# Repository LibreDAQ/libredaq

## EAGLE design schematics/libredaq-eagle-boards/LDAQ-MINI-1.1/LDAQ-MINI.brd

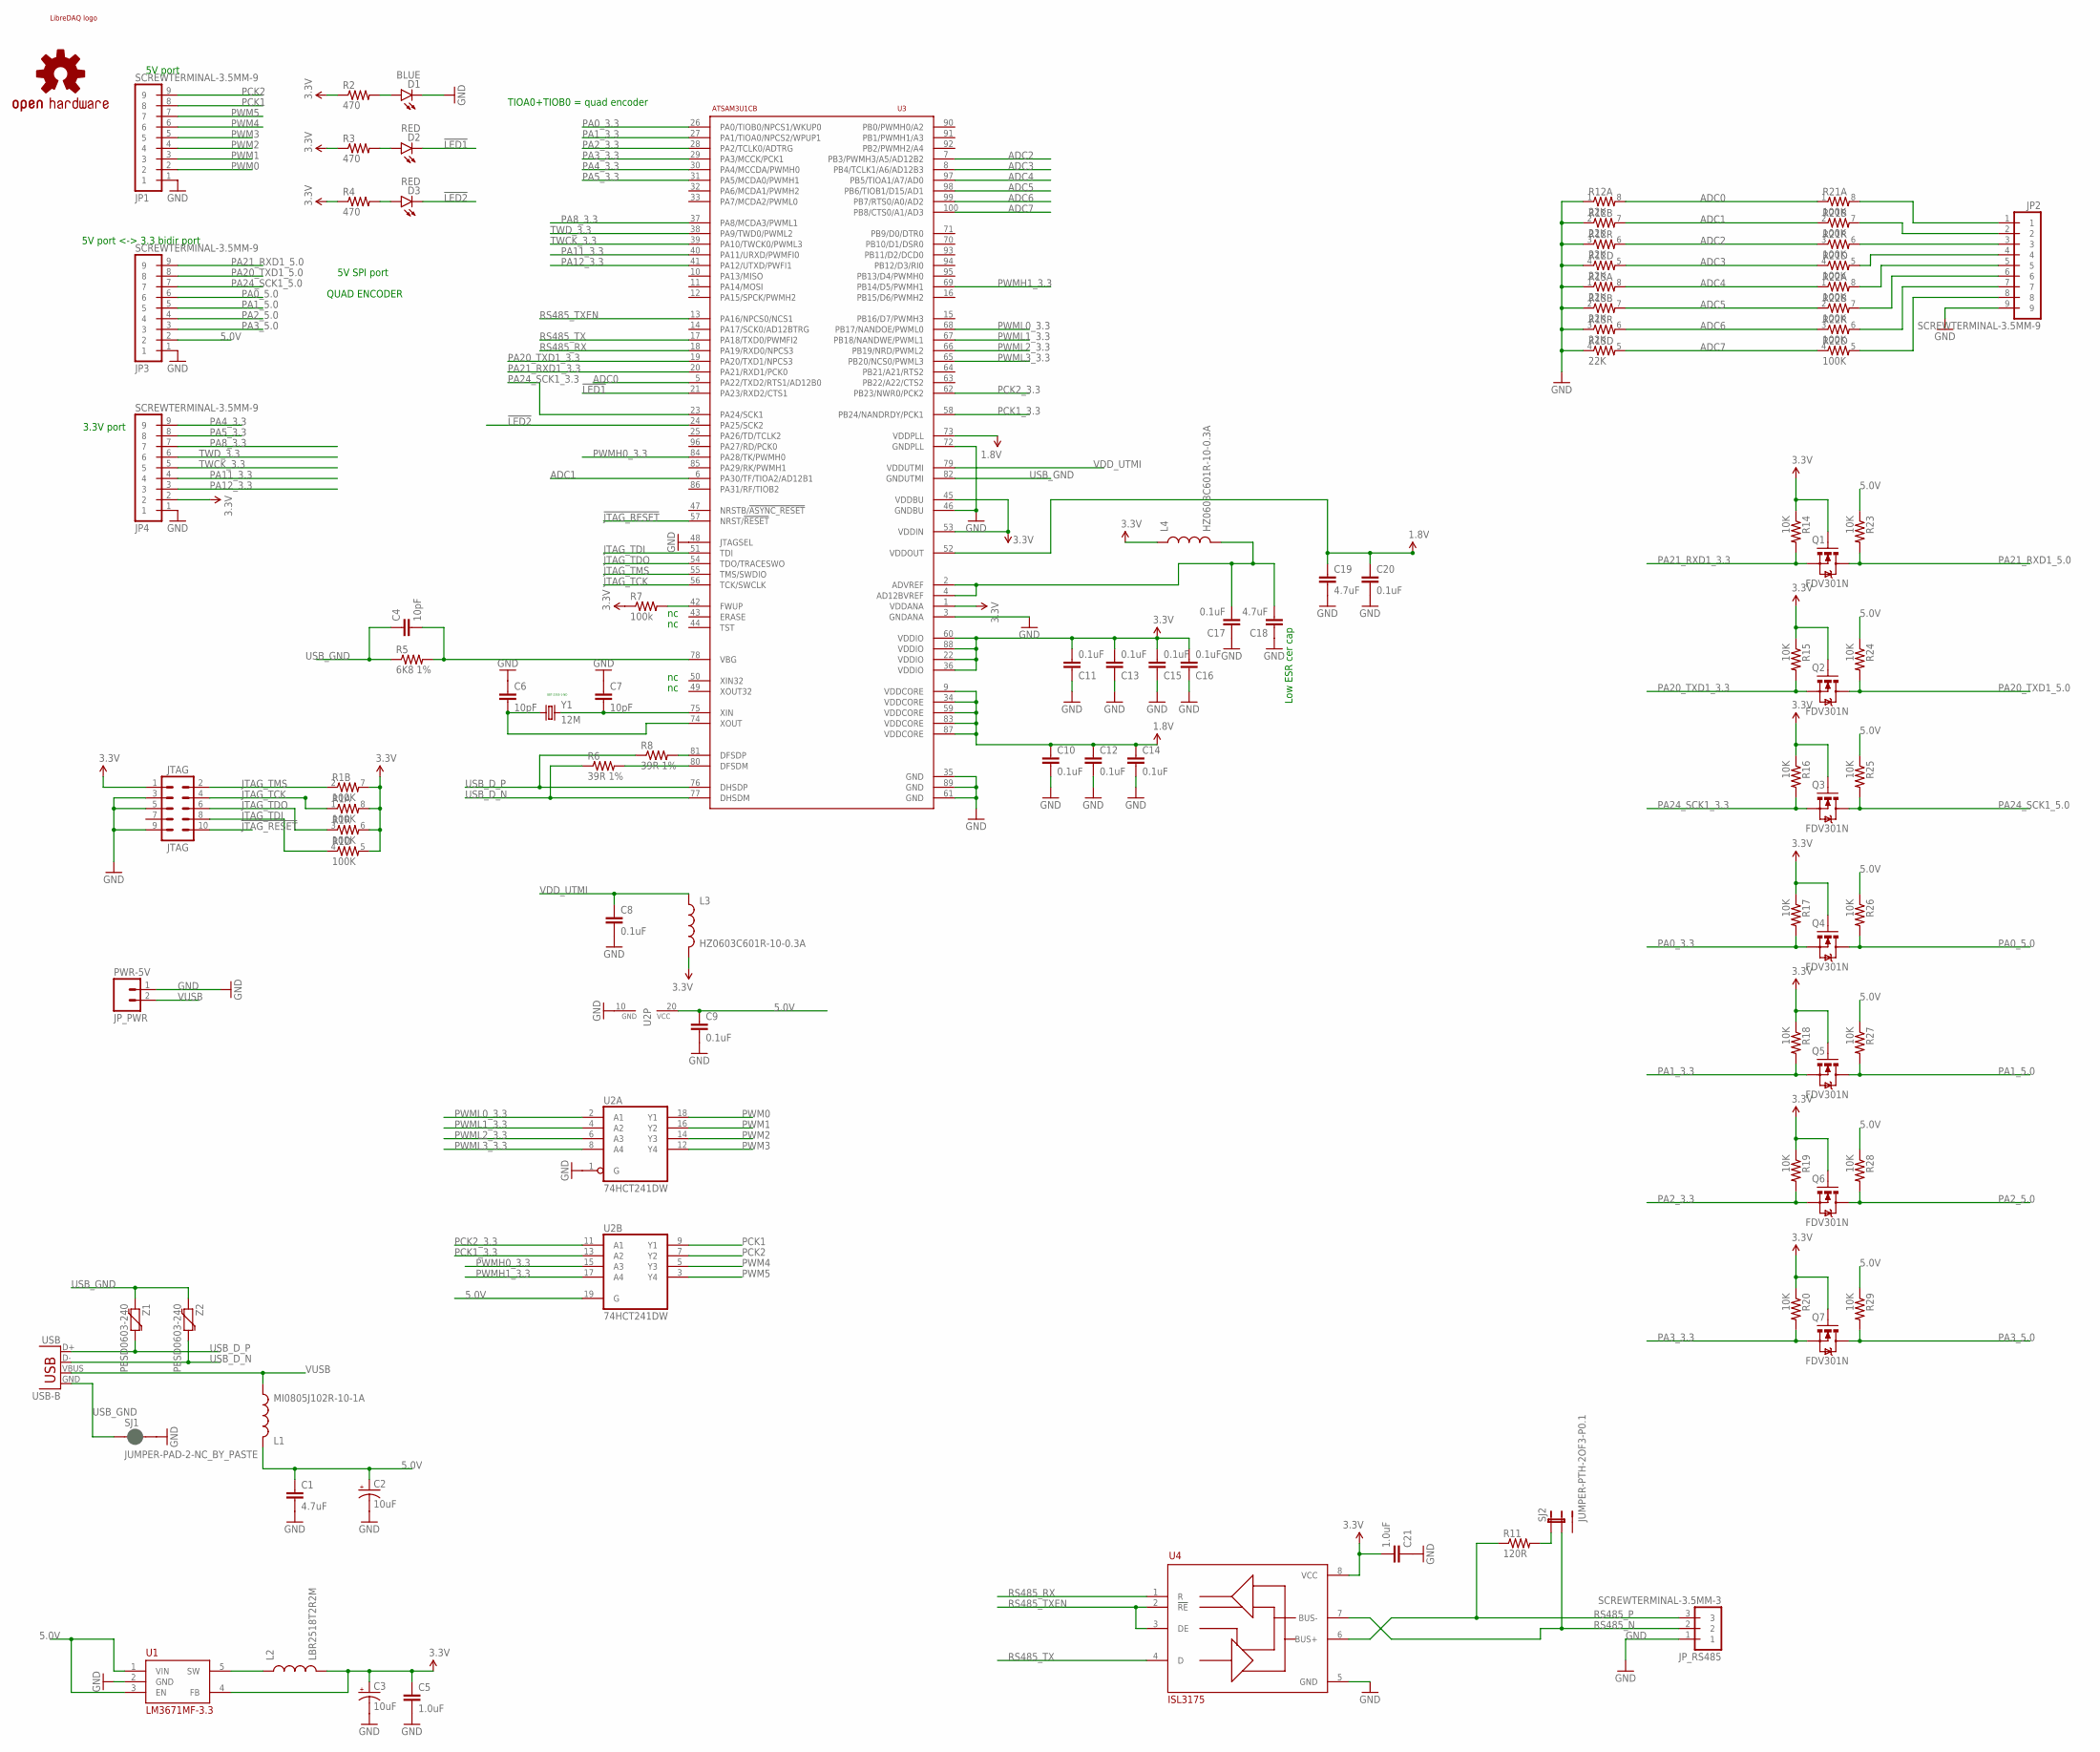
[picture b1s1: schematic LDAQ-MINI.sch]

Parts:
C1, C18, C19: 4.7uF; 0603-CAP
C2, C3: 10uF; EIA3216
C4, C6, C7: 10pF; 0603-CAP
C5: 1.0uF; 0805
C8, C9, C10, C11, C12, C13, C14, C15, C16, C17, C20: 0.1uF; 0603-CAP
C21: 1.0uF; 0603-CAP
D1: BLUE; LED-1206
D2, D3: RED; LED-1206
JP1, JP2, JP3, JP4: SCREWTERMINAL-3.5MM-9
JP_PWR: PWR-5V; JST-2-PTH-VERT
JP_RS485: SCREWTERMINAL-3.5MM-3
JTAG: JTAG; AVR_ICSP
L1: MI0805J102R-10-1A; 0805
L2: LBR2518T2R2M; 1007
L3, L4: HZ0603C601R-10-0.3A; 0603
LOGO1: LIBREDAQ_LOGO_MINILOGO_GENERIC; LIBREDAQ_LOGO
LOGO2: OSHW-LOGOL; OSHW-LOGO-L
Q1, Q2, Q3, Q4, Q5, Q6, Q7: FDV301N; SOT23-3
R1, R21, R22: 100K; 0603-ARV
R2, R3, R4: 470; 0603-RES
R5: 6K8 1%; 0603-RES
R6: 39R 1%; 0603-RES
R7: 100k; 0603-RES
R8: 39R 1%; 1206
R11: 120R; 0603-RES
R12, R13: 22K; 0603-ARV
R14, R15, R16, R17, R18, R19, R20, R23, R24, R25, R26, R27, R28, R29: 10K; 0603-RES
SJ1: JUMPER-PAD-2-NC_BY_PASTE; PAD-JUMPER-2-NC_BY_PASTE_YES_SILK
SJ2: JUMPER-PTH-2OF3-P0.1; 1X03_LONGPADS
U1: LM3671MF-3.3; TOP23-5
U2: 74HCT241DW; SO20W
U3: ATSAM3U1CB; TQFP100
U4: ISL3175; SOIC8
USB: USB-B; USB-B-PTH
Y1: 12M; CRYSTAL-SMD-5X3
Z1, Z2: PESD0603-240; 0603-RES

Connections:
1.8V: C10.1, C12.1, C14.1, C19.1, C20.1, U3.9 (VDDCORE), U3.34 (VDDCORE), U3.52 (VDDOUT), U3.59 (VDDCORE), U3.73 (VDDPLL), U3.83 (VDDCORE), U3.87 (VDDCORE)
3.3V: C3.A (+), C5.1, C11.2, C13.2, C15.2, C16.2, C21.2, JP4.2, JTAG.1, L2.2, L3.2, L4.1, Q1.1 (G), Q2.1 (G), Q3.1 (G), Q4.1 (G), Q5.1 (G), Q6.1 (G), Q7.1 (G), R1.5 (2), R1.6 (2), R1.7 (2), R1.8 (2), R2.1, R3.1, R4.1, R7.1, R14.1, R15.1, R16.1, R17.1, R18.1, R19.1, R20.1, U1.4 (FB), U3.1 (VDDANA), U3.22 (VDDIO), U3.36 (VDDIO), U3.45 (VDDBU), U3.53 (VDDIN), U3.60 (VDDIO), U3.88 (VDDIO), U4.8 (VCC)
5.0V: C1.1, C2.A (+), C9.1, JP3.2, L1.1, R23.1, R24.1, R25.1, R26.1, R27.1, R28.1, R29.1, U1.1 (VIN), U1.3 (EN), U2.19 (G), U2.20 (VCC)
!JTAG_RESET: JTAG.10, U3.57 (NRST/!RESET)
!LED1: D2.C, U3.21 (PA23/RXD2/CTS1)
!LED2: D3.C, U3.24 (PA25/SCK2)
ADC0: R12.8 (2), R21.1, U3.5 (PA22/TXD2/RTS1/AD12B0)
ADC1: R12.7 (2), R21.2 (1), U3.6 (PA30/TF/TIOA2/AD12B1)
ADC2: R12.6 (2), R21.3 (1), U3.7 (PB3/PWMH3/A5/AD12B2)
ADC3: R12.5 (2), R21.4 (1), U3.8 (PB4/TCLK1/A6/AD12B3)
ADC4: R13.8 (2), R22.1, U3.97 (PB5/TIOA1/A7/AD0)
ADC5: R13.7 (2), R22.2 (1), U3.98 (PB6/TIOB1/D15/AD1)
ADC6: R13.6 (2), R22.3 (1), U3.99 (PB7/RTS0/A0/AD2)
ADC7: R13.5 (2), R22.4 (1), U3.100 (PB8/CTS0/A1/AD3)
GND: C1.2, C2.C (-), C3.C (-), C5.2, C6.1, C7.1, C8.2, C9.2, C10.2, C11.1, C12.2, C13.1, C14.2, C15.1, C16.1, C17.1, C18.1, C19.2, C20.2, C21.1, D1.C, JP1.1, JP2.9, JP3.1, JP4.1, JP_PWR.1, JP_RS485.1, JTAG.3, JTAG.5, JTAG.9, R12.1, R12.2 (1), R12.3 (1), R12.4 (1), R13.1, R13.2 (1), R13.3 (1), R13.4 (1), SJ1.2, U1.2 (GND), U2.1 (G), U2.10 (GND), U3.3 (GNDANA), U3.35 (GND), U3.46 (GNDBU), U3.48 (JTAGSEL), U3.61 (GND), U3.72 (GNDPLL), U3.89 (GND), U4.5 (GND)
JTAG_TCK: JTAG.4, R1.1, U3.56 (TCK/SWCLK)
JTAG_TDI: JTAG.8, R1.4 (1), U3.51 (TDI)
JTAG_TDO: JTAG.6, R1.3 (1), U3.54 (TDO/TRACESWO)
JTAG_TMS: JTAG.2, R1.2 (1), U3.55 (TMS/SWDIO)
unnamed: C7.2, U3.75 (XIN), Y1.3 (2)
unnamed: C6.2, U3.74 (XOUT), Y1.1
unnamed: R8.2, U3.81 (DFSDP)
unnamed: R6.2, U3.80 (DFSDM)
unnamed: C4.2, R5.2, U3.78 (VBG)
unnamed: R7.2, U3.42 (FWUP)
unnamed: L2.1, U1.5 (SW)
unnamed: R11.2, SJ2.1
unnamed: JP2.1, R21.8 (2)
unnamed: JP2.2, R21.7 (2)
unnamed: JP2.3, R21.6 (2)
unnamed: JP2.4, R21.5 (2)
unnamed: JP2.5, R22.8 (2)
unnamed: JP2.6, R22.7 (2)
unnamed: JP2.7, R22.6 (2)
unnamed: JP2.8, R22.5 (2)
unnamed: C17.2, C18.2, L4.2, U3.2 (ADVREF), U3.4 (AD12BVREF)
unnamed: D2.A, R3.2
unnamed: D3.A, R4.2
unnamed: D1.A, R2.2
PA0_3.3: Q4.2 (S), R17.2, U3.26 (PA0/TIOB0/NPCS1/WKUP0)
PA0_5.0: JP3.6, Q4.3 (D), R26.2
PA1_3.3: Q5.2 (S), R18.2, U3.27 (PA1/TIOA0/NPCS2/WPUP1)
PA1_5.0: JP3.5, Q5.3 (D), R27.2
PA2_3.3: Q6.2 (S), R19.2, U3.28 (PA2/TCLK0/ADTRG)
PA2_5.0: JP3.4, Q6.3 (D), R28.2
PA3_3.3: Q7.2 (S), R20.2, U3.29 (PA3/MCCK/PCK1)
PA3_5.0: JP3.3, Q7.3 (D), R29.2
PA4_3.3: JP4.9, U3.30 (PA4/MCCDA/PWMH0)
PA5_3.3: JP4.8, U3.31 (PA5/MCDA0/PWMH1)
PA8_3.3: JP4.7, U3.37 (PA8/MCDA3/PWML1)
PA11_3.3: JP4.4, U3.40 (PA11/URXD/PWMFI0)
PA12_3.3: JP4.3, U3.41 (PA12/UTXD/PWFI1)
PA20_TXD1_3.3: Q2.2 (S), R15.2, U3.19 (PA20/TXD1/NPCS3)
PA20_TXD1_5.0: JP3.8, Q2.3 (D), R24.2
PA21_RXD1_3.3: Q1.2 (S), R14.2, U3.20 (PA21/RXD1/PCK0)
PA21_RXD1_5.0: JP3.9, Q1.3 (D), R23.2
PA24_SCK1_3.3: Q3.2 (S), R16.2, U3.23 (PA24/SCK1)
PA24_SCK1_5.0: JP3.7, Q3.3 (D), R25.2
PCK1: JP1.8, U2.9 (Y1)
PCK1_3.3: U2.13 (A2), U3.58 (PB24/NANDRDY/PCK1)
PCK2: JP1.9, U2.7 (Y2)
PCK2_3.3: U2.11 (A1), U3.62 (PB23/NWR0/PCK2)
PWM0: JP1.2, U2.18 (Y1)
PWM1: JP1.3, U2.16 (Y2)
PWM2: JP1.4, U2.14 (Y3)
PWM3: JP1.5, U2.12 (Y4)
PWM4: JP1.6, U2.5 (Y3)
PWM5: JP1.7, U2.3 (Y4)
PWMH0_3.3: U2.15 (A3), U3.84 (PA28/TK/PWMH0)
PWMH1_3.3: U2.17 (A4), U3.69 (PB14/D5/PWMH1)
PWML0_3.3: U2.2 (A1), U3.68 (PB17/NANDOE/PWML0)
PWML1_3.3: U2.4 (A2), U3.67 (PB18/NANDWE/PWML1)
PWML2_3.3: U2.6 (A3), U3.66 (PB19/NRD/PWML2)
PWML3_3.3: U2.8 (A4), U3.65 (PB20/NCS0/PWML3)
RS485_N: JP_RS485.2, SJ2.2, U4.7 (BUS-)
RS485_P: JP_RS485.3, R11.1, U4.6 (BUS+)
RS485_RX: U3.18 (PA19/RXD0/NPCS3), U4.1 (R)
RS485_TX: U3.17 (PA18/TXD0/PWMFI2), U4.4 (D)
RS485_TXEN: U3.13 (PA16/NPCS0/NCS1), U4.2 (!RE), U4.3 (DE)
TWCK_3.3: JP4.5, U3.39 (PA10/TWCK0/PWML3)
TWD_3.3: JP4.6, U3.38 (PA9/TWD0/PWML2)
USB_D_N: R6.1, U3.77 (DHSDM), USB.D-, Z2.2
USB_D_P: R8.1, U3.76 (DHSDP), USB.D+, Z1.2
USB_GND: C4.1, R5.1, SJ1.1, U3.82 (GNDUTMI), USB.GND, Z1.1, Z2.1
VDD_UTMI: C8.1, L3.1, U3.79 (VDDUTMI)
VUSB: JP_PWR.2, L1.2, USB.VBUS

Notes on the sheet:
887-2355-1-ND
Low ESR cer cap
5V port
5V port <-> 3.3 bidir port
3.3V port
TIOA0+TIOB0 = quad encoder
5V SPI port
QUAD ENCODER

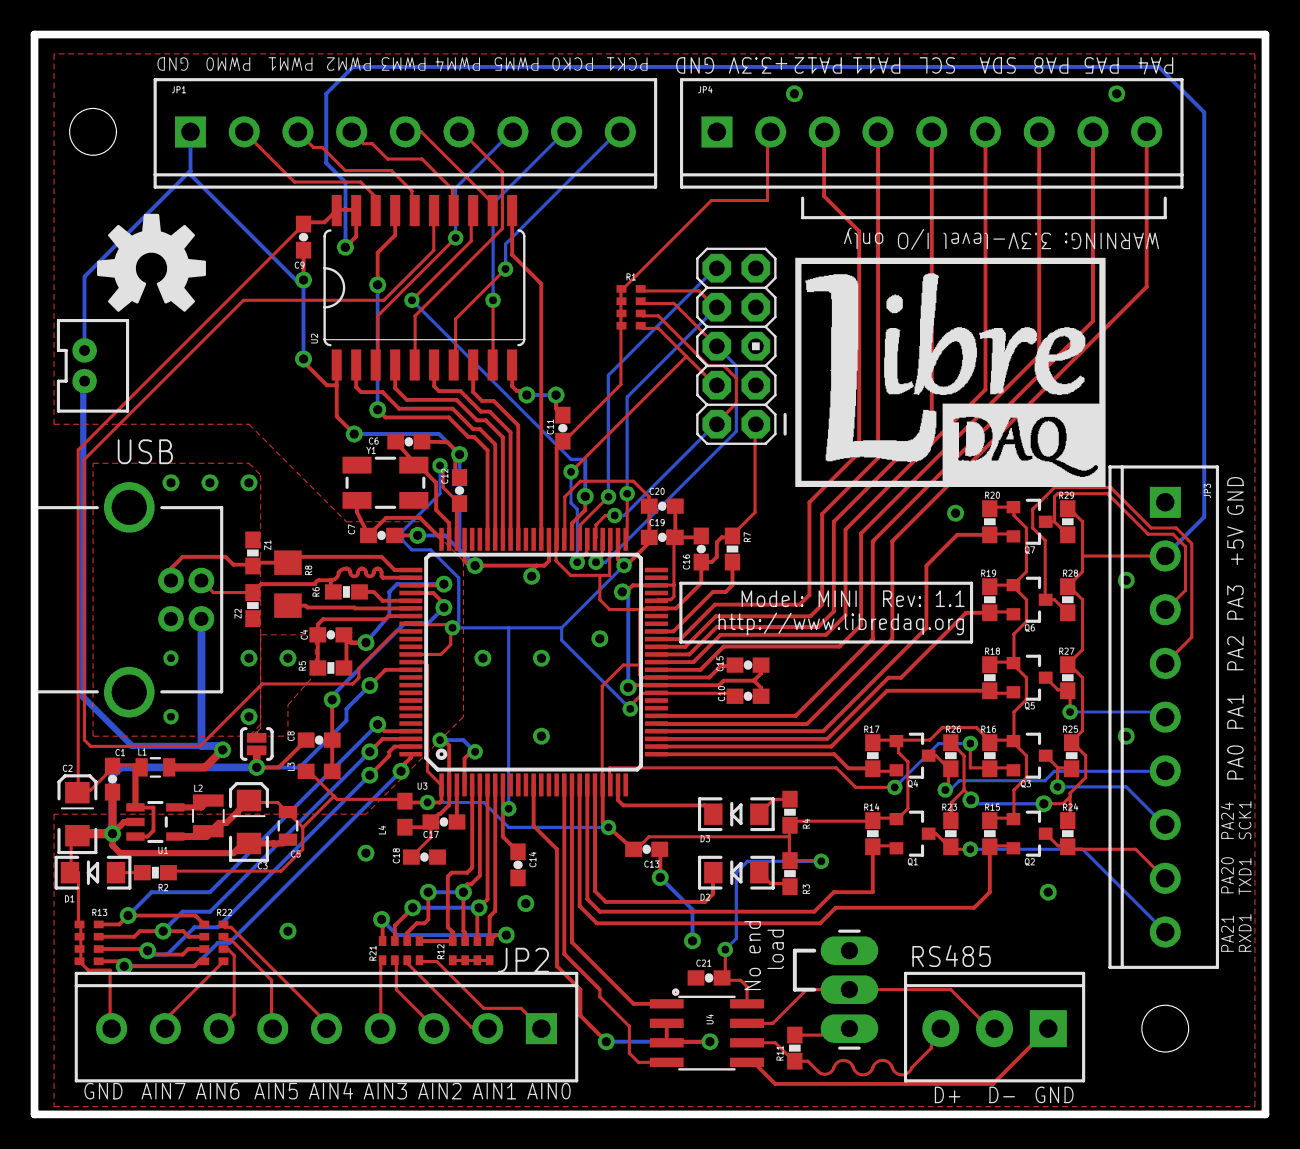
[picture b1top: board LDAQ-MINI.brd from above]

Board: 2 copper layers, 80.2 x 70.3 mm, 83 parts (0 on the bottom side), 86 nets.

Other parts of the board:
U$2, U$4: STAND-OFF-TIGHT

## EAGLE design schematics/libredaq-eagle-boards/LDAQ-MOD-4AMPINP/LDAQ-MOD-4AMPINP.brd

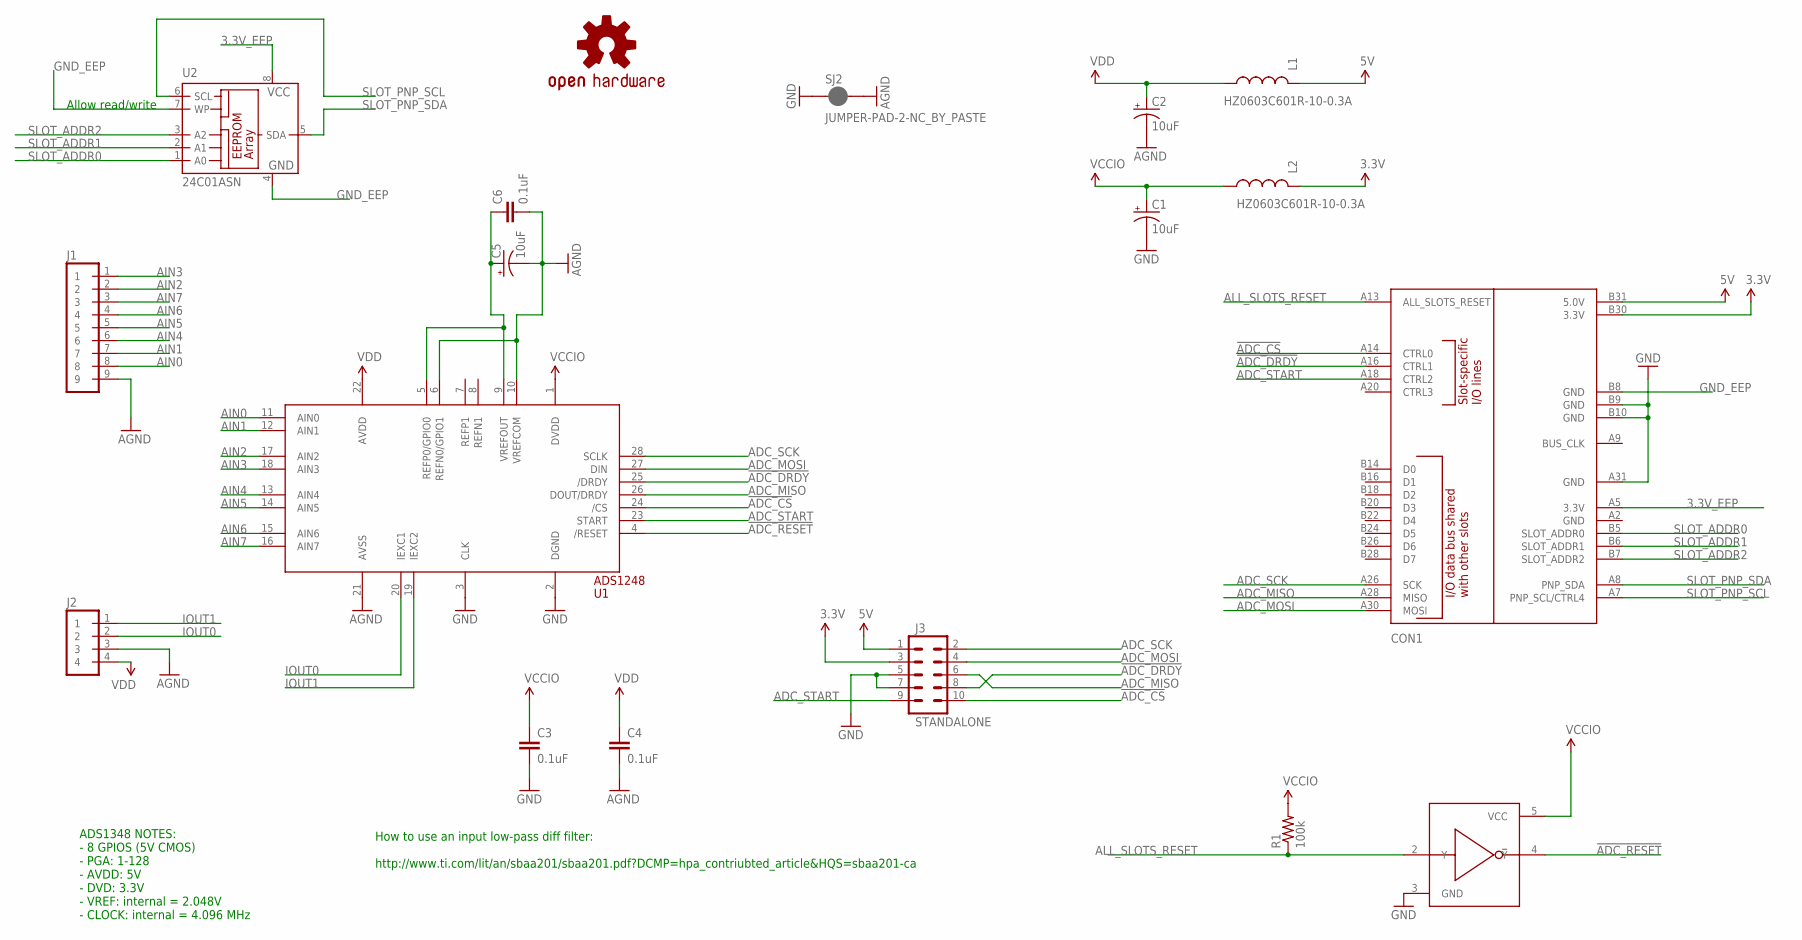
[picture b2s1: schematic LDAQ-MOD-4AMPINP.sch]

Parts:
C1, C2, C5: 10uF; EIA3216
C3, C4, C6: 0.1uF; 0603-CAP
CON1: BOARD; PCI-E_64_EDGE_63X50_PADS-ONLY
J1: SCREWTERMINAL-3.5MM-9
J2: SCREWTERMINAL-3.5MM-4
J3: STANDALONE; AVR_ICSP
L1, L2: HZ0603C601R-10-0.3A; 0603
LOGO1: OSHW-LOGOL; OSHW-LOGO-L
R1: 100k; 0603-RES
SJ2: JUMPER-PAD-2-NC_BY_PASTE; PAD-JUMPER-2-NC_BY_PASTE_YES_SILK
U1: ADS1248; TSSOP-28_4MM
U2: 24C01ASN; SO-08
U3: 74AHCT1G04; SOT353-SC70-5

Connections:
3.3V: CON1.B30 (3.3V), J3.3, L2.1
3.3V_EEP: CON1.A5 (3.3V), U2.8 (VCC)
5V: CON1.B31 (5.0V), J3.1, L1.1
!ADC_CS: CON1.A14 (CTRL0), J3.10, U1.24 (/CS)
!ADC_DRDY: CON1.A16 (CTRL1), J3.8, U1.25 (/DRDY)
!ADC_RESET: U1.4 (/RESET), U3.4 (!Y)
ADC_MISO: CON1.A28 (MISO), J3.6, U1.26 (DOUT/DRDY)
ADC_MOSI: CON1.A30 (MOSI), J3.4, U1.27 (DIN)
ADC_SCK: CON1.A26 (SCK), J3.2, U1.28 (SCLK)
ADC_START: CON1.A18 (CTRL2), J3.9, U1.23 (START)
AGND: C2.C (-), C4.2, C5.C (-), C6.2, J1.9, J2.3, SJ2.2, U1.6 (REFN0/GPIO1), U1.10 (VREFCOM), U1.21 (AVSS)
AIN0: J1.8, U1.11 (AIN0)
AIN1: J1.7, U1.12 (AIN1)
AIN2: J1.2, U1.17 (AIN2)
AIN3: J1.1, U1.18 (AIN3)
AIN4: J1.6, U1.13 (AIN4)
AIN5: J1.5, U1.14 (AIN5)
AIN6: J1.4, U1.15 (AIN6)
AIN7: J1.3, U1.16 (AIN7)
ALL_SLOTS_RESET: CON1.A13 (ALL_SLOTS_RESET), R1.1, U3.2 (Y)
GND: C1.C (-), C3.2, CON1.A31 (GND), CON1.B9 (GND), CON1.B10 (GND), J3.5, J3.7, SJ2.1, U1.2 (DGND), U1.3 (CLK), U3.3 (GND)
GND_EEP: CON1.B8 (GND), U2.4 (GND), U2.7 (WP)
IOUT0: J2.2, U1.20 (IEXC1)
IOUT1: J2.1, U1.19 (IEXC2)
unnamed: C5.A (+), C6.1, U1.5 (REFP0/GPIO0), U1.9 (VREFOUT)
SLOT_ADDR0: CON1.B5 (SLOT_ADDR0), U2.1 (A0)
SLOT_ADDR1: CON1.B6 (SLOT_ADDR1), U2.2 (A1)
SLOT_ADDR2: CON1.B7 (SLOT_ADDR2), U2.3 (A2)
SLOT_PNP_SCL: CON1.A7 (PNP_SCL/CTRL4), U2.6 (SCL)
SLOT_PNP_SDA: CON1.A8 (PNP_SDA), U2.5 (SDA)
VCCIO: C1.A (+), C3.1, L2.2, R1.2, U1.1 (DVDD), U3.5 (VCC)
VDD: C2.A (+), C4.1, J2.4, L1.2, U1.22 (AVDD)

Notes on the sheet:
Allow read/write
ADS1348 NOTES: - 8 GPIOS (5V CMOS) - PGA: 1-128 - AVDD: 5V - DVD: 3.3V - VREF: internal = 2.048V - CLOCK: internal = 4.096 MHz
How to use an input low-pass diff filter: http://www.ti.com/lit/an/sbaa201/sbaa201.pdf?DCMP=hpa_contriubted_article&HQS=sbaa201-ca

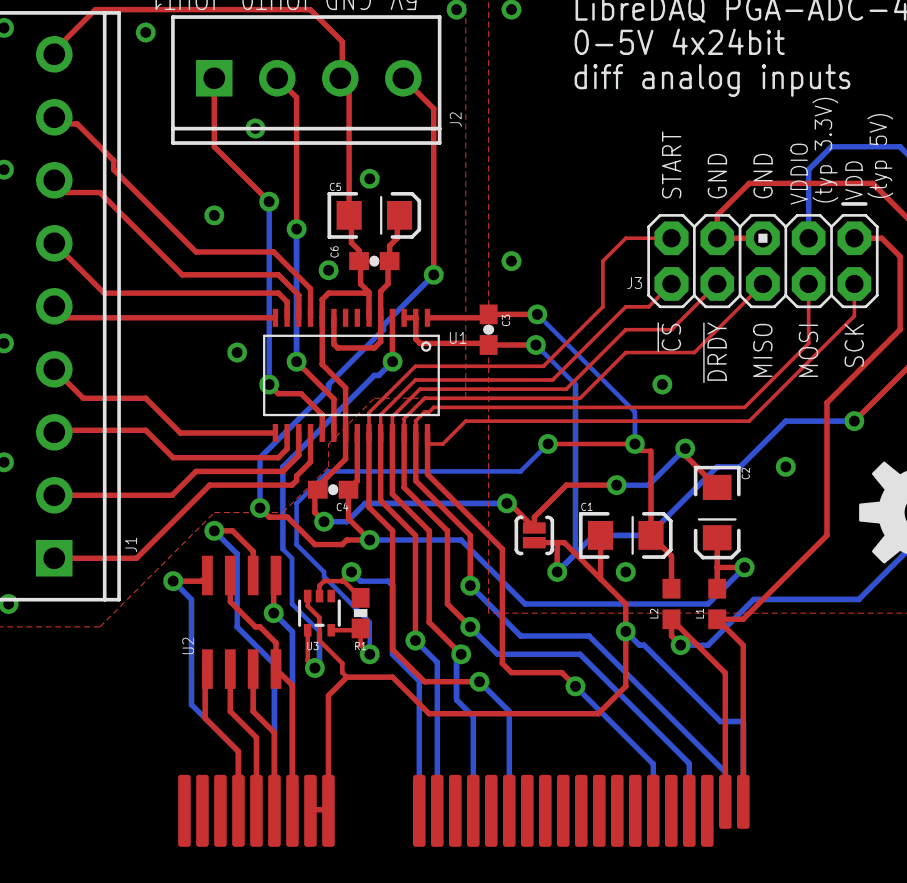
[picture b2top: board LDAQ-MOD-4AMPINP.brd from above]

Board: 2 copper layers, 18 parts (0 on the bottom side), 32 nets.

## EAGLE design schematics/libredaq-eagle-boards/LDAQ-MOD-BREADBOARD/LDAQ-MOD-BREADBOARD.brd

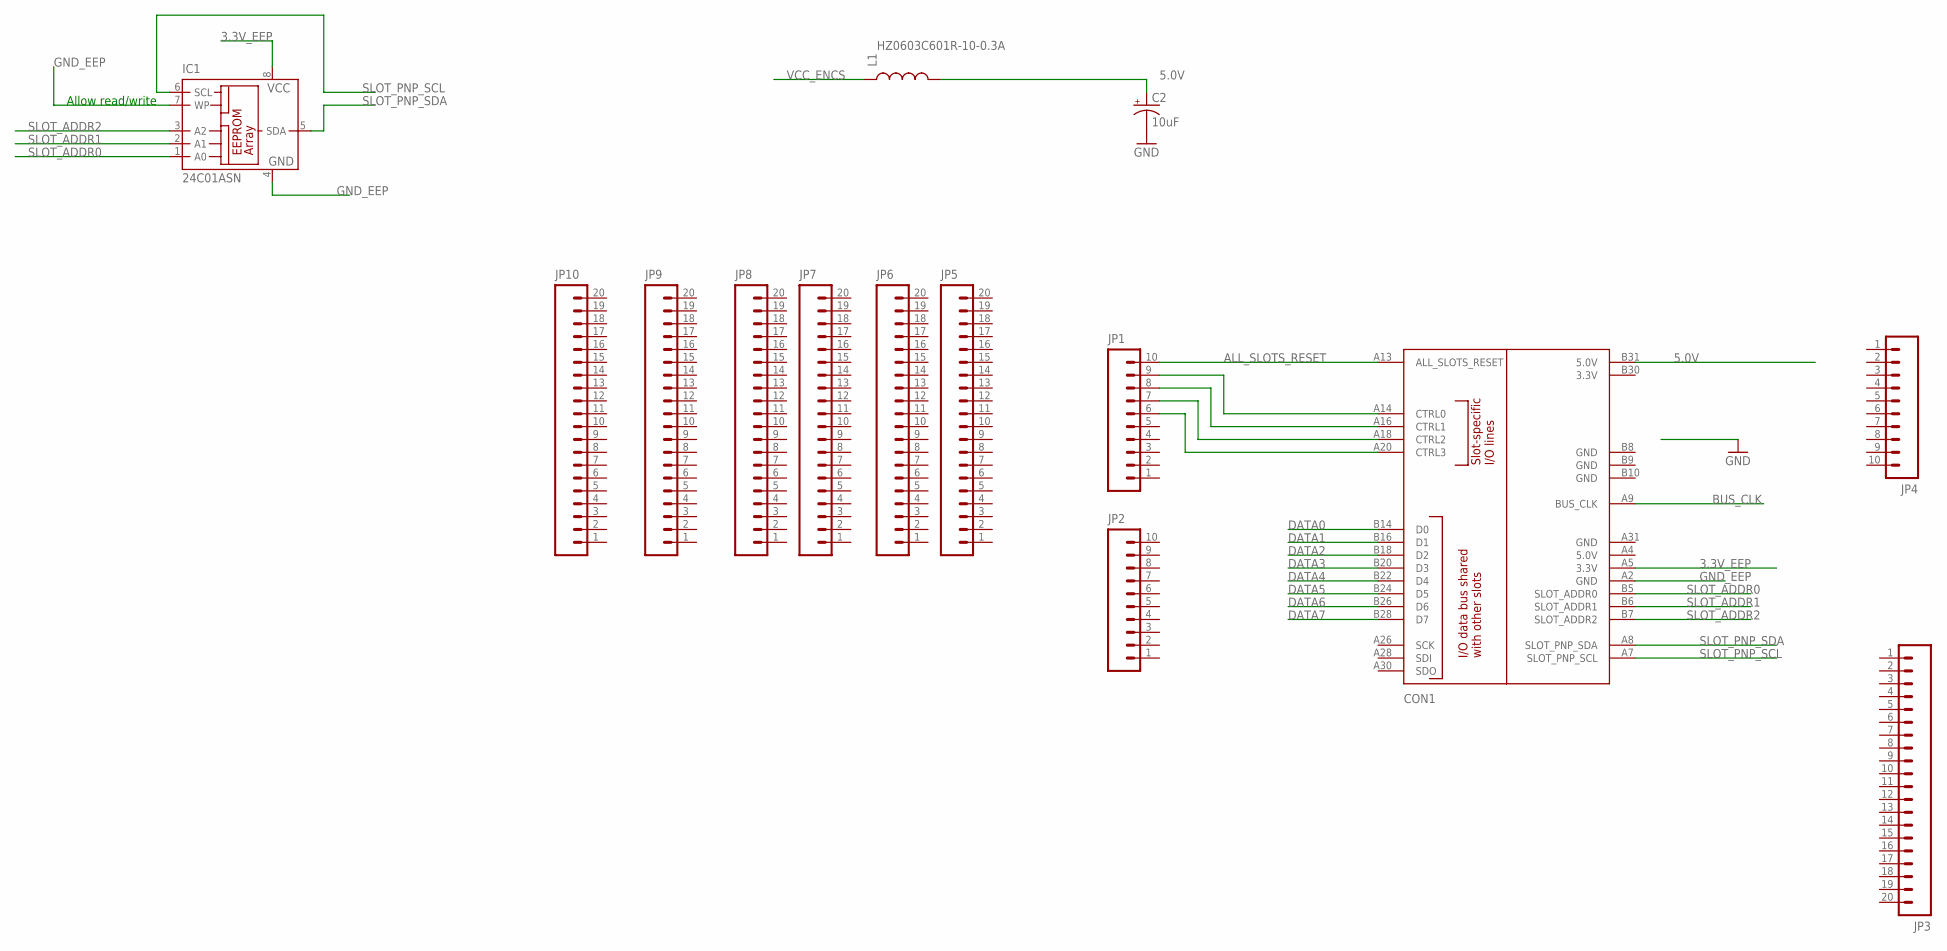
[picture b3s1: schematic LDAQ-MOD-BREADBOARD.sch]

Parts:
C2: 10uF; EIA3216
CON1: BOARD; PCI-E_64_EDGE_70X60
IC1: 24C01ASN; SO-08
JP1, JP2, JP4: M10NO_SILK_PTH_FEMALE; 1X10_NO_SILK
JP3, JP5, JP6, JP7, JP8, JP9, JP10: M20; 1X20
L1: HZ0603C601R-10-0.3A; 0603

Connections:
3.3V_EEP: CON1.A5 (3.3V), IC1.8 (VCC)
5.0V: C2.A (+), CON1.B31 (5.0V), L1.2
ALL_SLOTS_RESET: CON1.A13 (ALL_SLOTS_RESET), JP1.10
BUS_CLK: CON1.A9 (BUS_CLK)
DATA0: CON1.B14 (D0)
DATA1: CON1.B16 (D1)
DATA2: CON1.B18 (D2)
DATA3: CON1.B20 (D3)
DATA4: CON1.B22 (D4)
DATA5: CON1.B24 (D5)
DATA6: CON1.B26 (D6)
DATA7: CON1.B28 (D7)
GND: C2.C (-)
GND_EEP: CON1.A2 (GND), IC1.4 (GND), IC1.7 (WP)
unnamed: CON1.A14 (CTRL0), JP1.9
unnamed: CON1.A16 (CTRL1), JP1.8
unnamed: CON1.A18 (CTRL2), JP1.7
unnamed: CON1.A20 (CTRL3), JP1.6
SLOT_ADDR0: CON1.B5 (SLOT_ADDR0), IC1.1 (A0)
SLOT_ADDR1: CON1.B6 (SLOT_ADDR1), IC1.2 (A1)
SLOT_ADDR2: CON1.B7 (SLOT_ADDR2), IC1.3 (A2)
SLOT_PNP_SCL: CON1.A7 (SLOT_PNP_SCL), IC1.6 (SCL)
SLOT_PNP_SDA: CON1.A8 (SLOT_PNP_SDA), IC1.5 (SDA)
VCC_ENCS: L1.1

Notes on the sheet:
Allow read/write

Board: 2 copper layers, 14 parts (0 on the bottom side), 13 nets, no tracks yet.

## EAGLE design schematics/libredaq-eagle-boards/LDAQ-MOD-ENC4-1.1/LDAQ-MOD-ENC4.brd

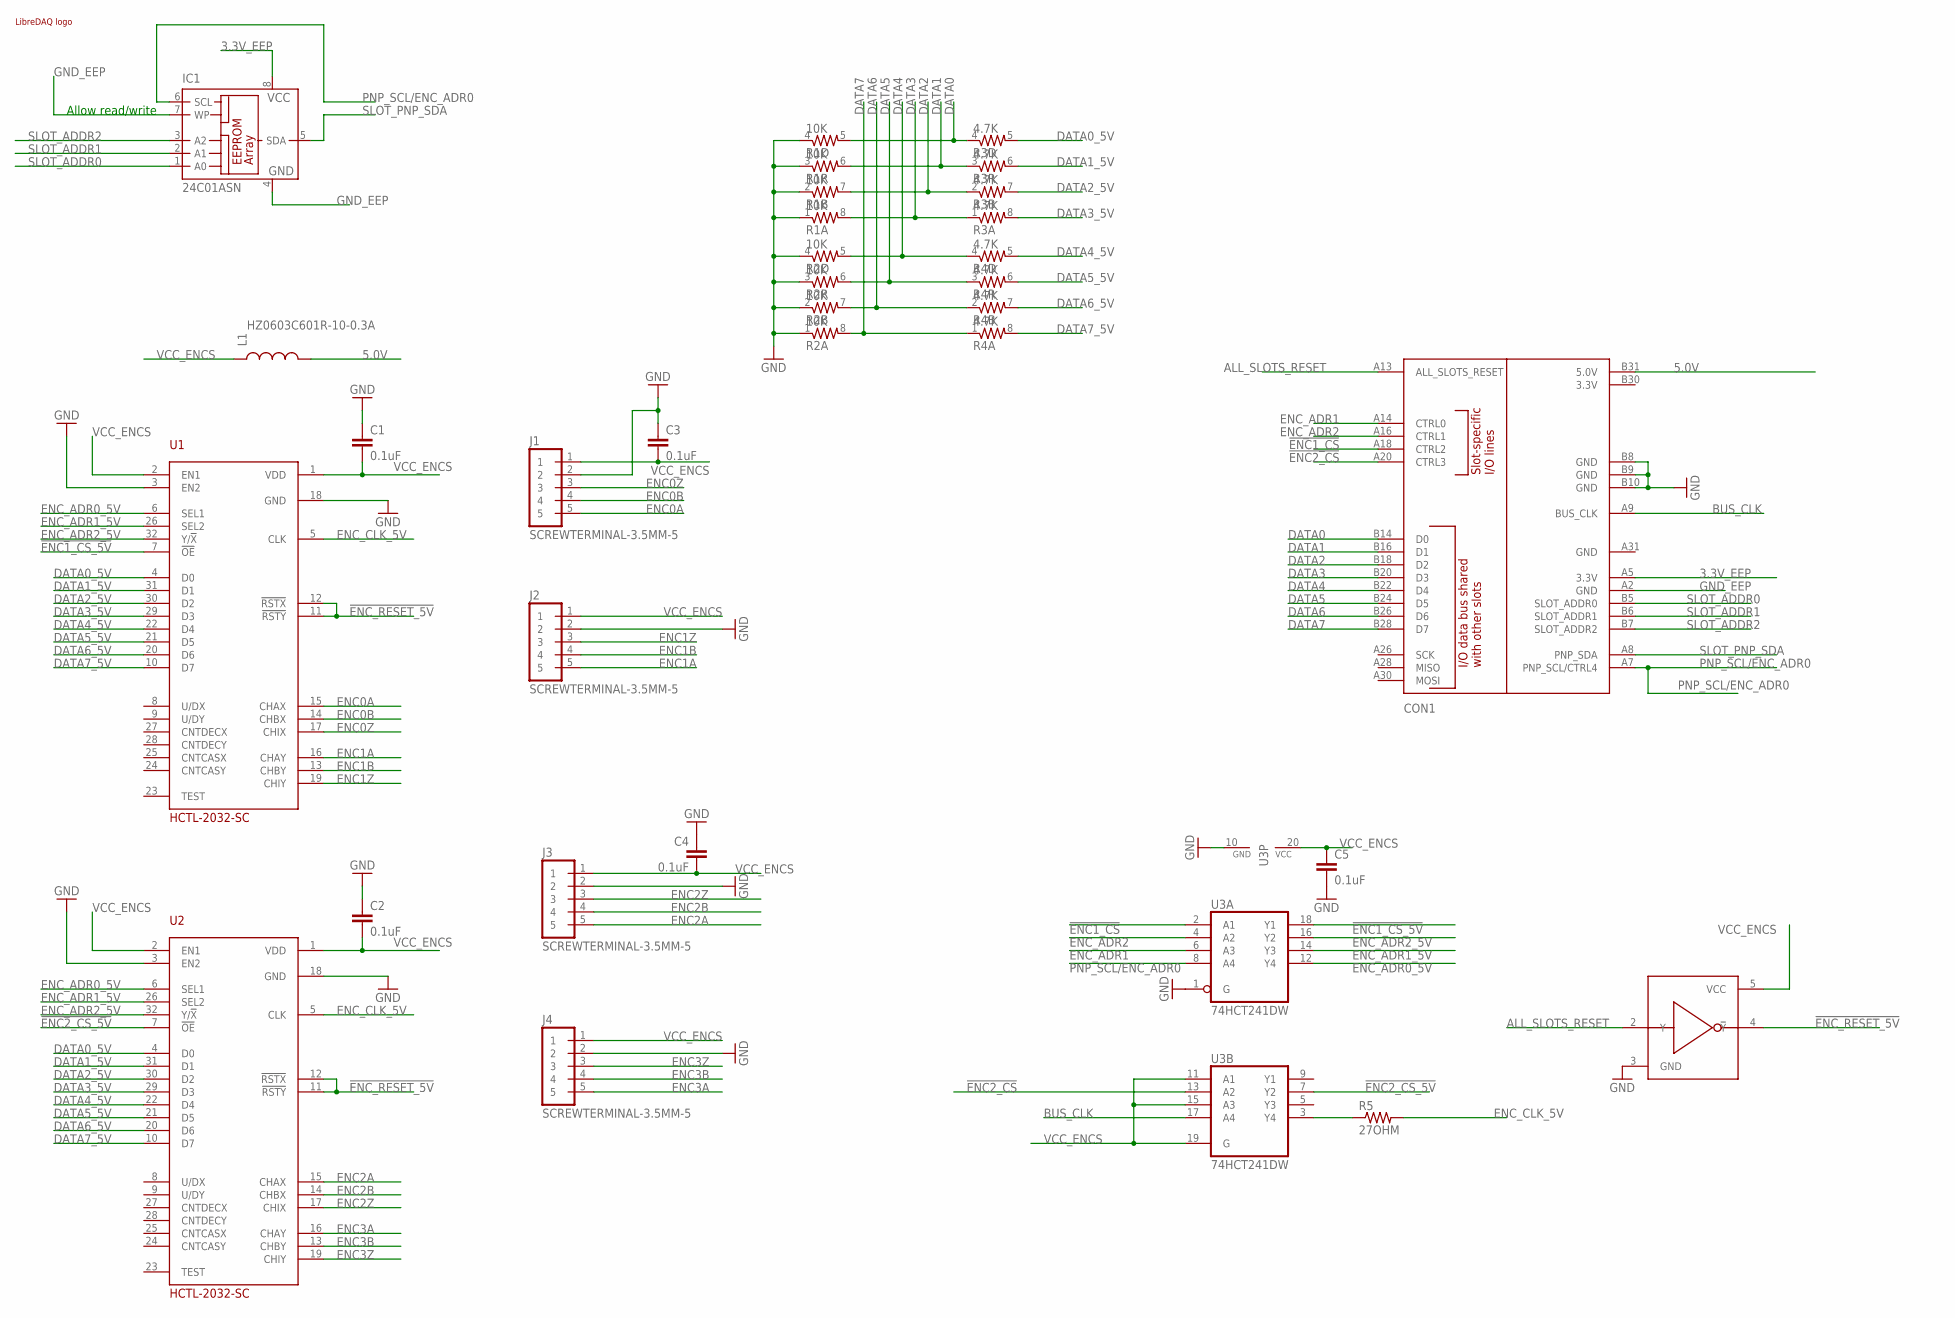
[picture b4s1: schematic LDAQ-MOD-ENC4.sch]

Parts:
C1, C2, C3, C4, C5: 0.1uF; 0603-CAP
CON1: BOARD; PCI-E_64_EDGE_70X60_PADS-ONLY
IC1: 24C01ASN; SO-08
J1, J2, J3, J4: SCREWTERMINAL-3.5MM-5
L1: HZ0603C601R-10-0.3A; 0603
LOGO1: LIBREDAQ_LOGO_MINILOGO_GENERIC; LIBREDAQ_LOGO
R1, R2: 10K; 0603-ARV
R3, R4: 4.7K; 0603-ARV
R5: 27OHM; 0603
U1, U2: HCTL-2032-SC; SOIC32
U3: 74HCT241DW; SO20W
U4: 74AHCT1G04; SOT353-SC70-5

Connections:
3.3V_EEP: CON1.A5 (3.3V), IC1.8 (VCC)
5.0V: CON1.B31 (5.0V), L1.2
!ENC1_CS: CON1.A18 (CTRL2), U3.2 (A1)
!ENC1_CS_5V: U1.7 (!OE), U3.18 (Y1)
!ENC2_CS: CON1.A20 (CTRL3), U3.13 (A2)
!ENC2_CS_5V: U2.7 (!OE), U3.7 (Y2)
!ENC_RESET_5V: U1.11 (!RSTY), U1.12 (!RSTX), U2.11 (!RSTY), U2.12 (!RSTX), U4.4 (!Y)
ALL_SLOTS_RESET: CON1.A13 (ALL_SLOTS_RESET), U4.2 (Y)
BUS_CLK: CON1.A9 (BUS_CLK), U3.17 (A4)
DATA0: CON1.B14 (D0), R1.5 (2), R3.4 (1)
DATA0_5V: R3.5 (2), U1.4 (D0), U2.4 (D0)
DATA1: CON1.B16 (D1), R1.6 (2), R3.3 (1)
DATA1_5V: R3.6 (2), U1.31 (D1), U2.31 (D1)
DATA2: CON1.B18 (D2), R1.7 (2), R3.2 (1)
DATA2_5V: R3.7 (2), U1.30 (D2), U2.30 (D2)
DATA3: CON1.B20 (D3), R1.8 (2), R3.1
DATA3_5V: R3.8 (2), U1.29 (D3), U2.29 (D3)
DATA4: CON1.B22 (D4), R2.5 (2), R4.4 (1)
DATA4_5V: R4.5 (2), U1.22 (D4), U2.22 (D4)
DATA5: CON1.B24 (D5), R2.6 (2), R4.3 (1)
DATA5_5V: R4.6 (2), U1.21 (D5), U2.21 (D5)
DATA6: CON1.B26 (D6), R2.7 (2), R4.2 (1)
DATA6_5V: R4.7 (2), U1.20 (D6), U2.20 (D6)
DATA7: CON1.B28 (D7), R2.8 (2), R4.1
DATA7_5V: R4.8 (2), U1.10 (D7), U2.10 (D7)
ENC0A: J1.5, U1.15 (CHAX)
ENC0B: J1.4, U1.14 (CHBX)
ENC0Z: J1.3, U1.17 (CHIX)
ENC1A: J2.5, U1.16 (CHAY)
ENC1B: J2.4, U1.13 (CHBY)
ENC1Z: J2.3, U1.19 (CHIY)
ENC2A: J3.5, U2.15 (CHAX)
ENC2B: J3.4, U2.14 (CHBX)
ENC2Z: J3.3, U2.17 (CHIX)
ENC3A: J4.5, U2.16 (CHAY)
ENC3B: J4.4, U2.13 (CHBY)
ENC3Z: J4.3, U2.19 (CHIY)
ENC_ADR0_5V: U1.6 (SEL1), U2.6 (SEL1), U3.12 (Y4)
ENC_ADR1: CON1.A14 (CTRL0), U3.6 (A3)
ENC_ADR1_5V: U1.26 (SEL2), U2.26 (SEL2), U3.14 (Y3)
ENC_ADR2: CON1.A16 (CTRL1), U3.4 (A2)
ENC_ADR2_5V: U1.32 (Y/!X), U2.32 (Y/!X), U3.16 (Y2)
ENC_CLK_5V: R5.2, U1.5 (CLK), U2.5 (CLK)
GND: C1.1, C2.1, C3.1, C4.1, C5.2, CON1.B8 (GND), CON1.B9 (GND), CON1.B10 (GND), J1.2, J2.2, J3.2, J4.2, R1.1, R1.2 (1), R1.3 (1), R1.4 (1), R2.1, R2.2 (1), R2.3 (1), R2.4 (1), U1.3 (EN2), U1.18 (GND), U2.3 (EN2), U2.18 (GND), U3.1 (G), U3.10 (GND), U4.3 (GND)
GND_EEP: CON1.A2 (GND), IC1.4 (GND), IC1.7 (WP)
unnamed: R5.1, U3.3 (Y4)
PNP_SCL/ENC_ADR0: CON1.A7 (PNP_SCL/CTRL4), IC1.6 (SCL), U3.8 (A4)
SLOT_ADDR0: CON1.B5 (SLOT_ADDR0), IC1.1 (A0)
SLOT_ADDR1: CON1.B6 (SLOT_ADDR1), IC1.2 (A1)
SLOT_ADDR2: CON1.B7 (SLOT_ADDR2), IC1.3 (A2)
SLOT_PNP_SDA: CON1.A8 (PNP_SDA), IC1.5 (SDA)
VCC_ENCS: C1.2, C2.2, C3.2, C4.2, C5.1, J1.1, J2.1, J3.1, J4.1, L1.1, U1.1 (VDD), U1.2 (EN1), U2.1 (VDD), U2.2 (EN1), U3.11 (A1), U3.15 (A3), U3.19 (G), U3.20 (VCC), U4.5 (VCC)

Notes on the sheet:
Allow read/write

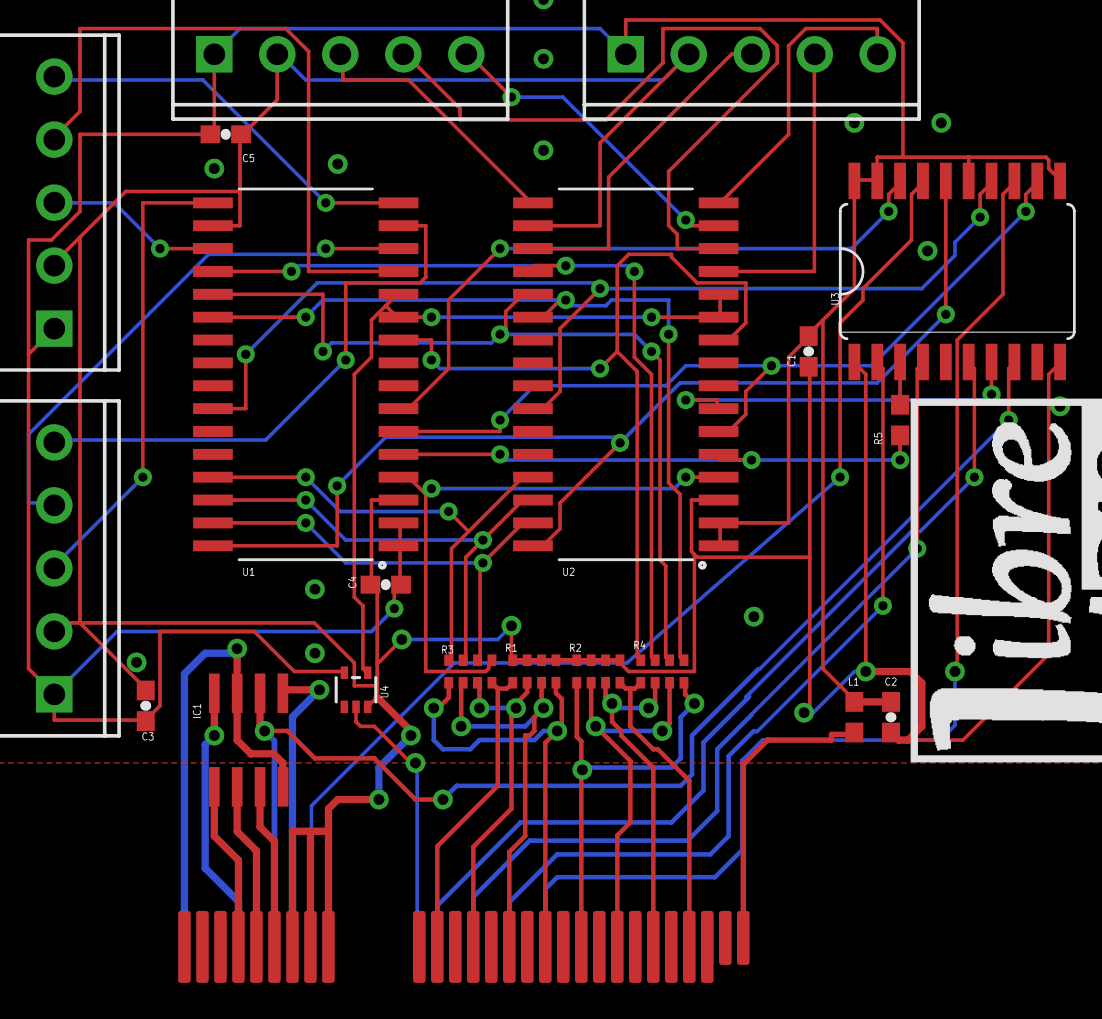
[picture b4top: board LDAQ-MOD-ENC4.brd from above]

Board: 2 copper layers, 22 parts (0 on the bottom side), 52 nets.

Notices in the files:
parts and their libraries:
SparkFun-Connectors: Licensing: Creative Commons ShareAlike 4.0 International - https://creativecommons.org/licenses/by-sa/4.0
libredaq-comps: Jose-Luis Blanco (C) 2015
